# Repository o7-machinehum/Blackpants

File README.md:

# Blackpants
The Blackpants are a carrier board for the [Flipper Blackhat](https://github.com/o7-machinehum/flipper-blackhat). They remove the need for the Flipper Zero itself. This repository was forked from the WHY2025 badge.

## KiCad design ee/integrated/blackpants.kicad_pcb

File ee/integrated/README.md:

# Blackpants hardware

Open **blackpants.kicad_pro** for the active A523 schematic and PCB. It replaces
the A33 hierarchy and uses AXP717C + AXP323 with 2GB LPDDR4.

- [Schematic review PDF](capture/review.pdf)
- [Capture status and interface mapping](capture/README.md)
- [Six-layer layout status and previews](layout/README.md)
- [RAM sourcing](LPDDR4/sourcing.md)
- [Source documents](../../docs/a523/README.md)

All 65 SoC-to-RAM signal paths are connected. There are 139 open connections
overall. Routing remains incomplete; DDR timing and signal/power integrity
have not been approved.

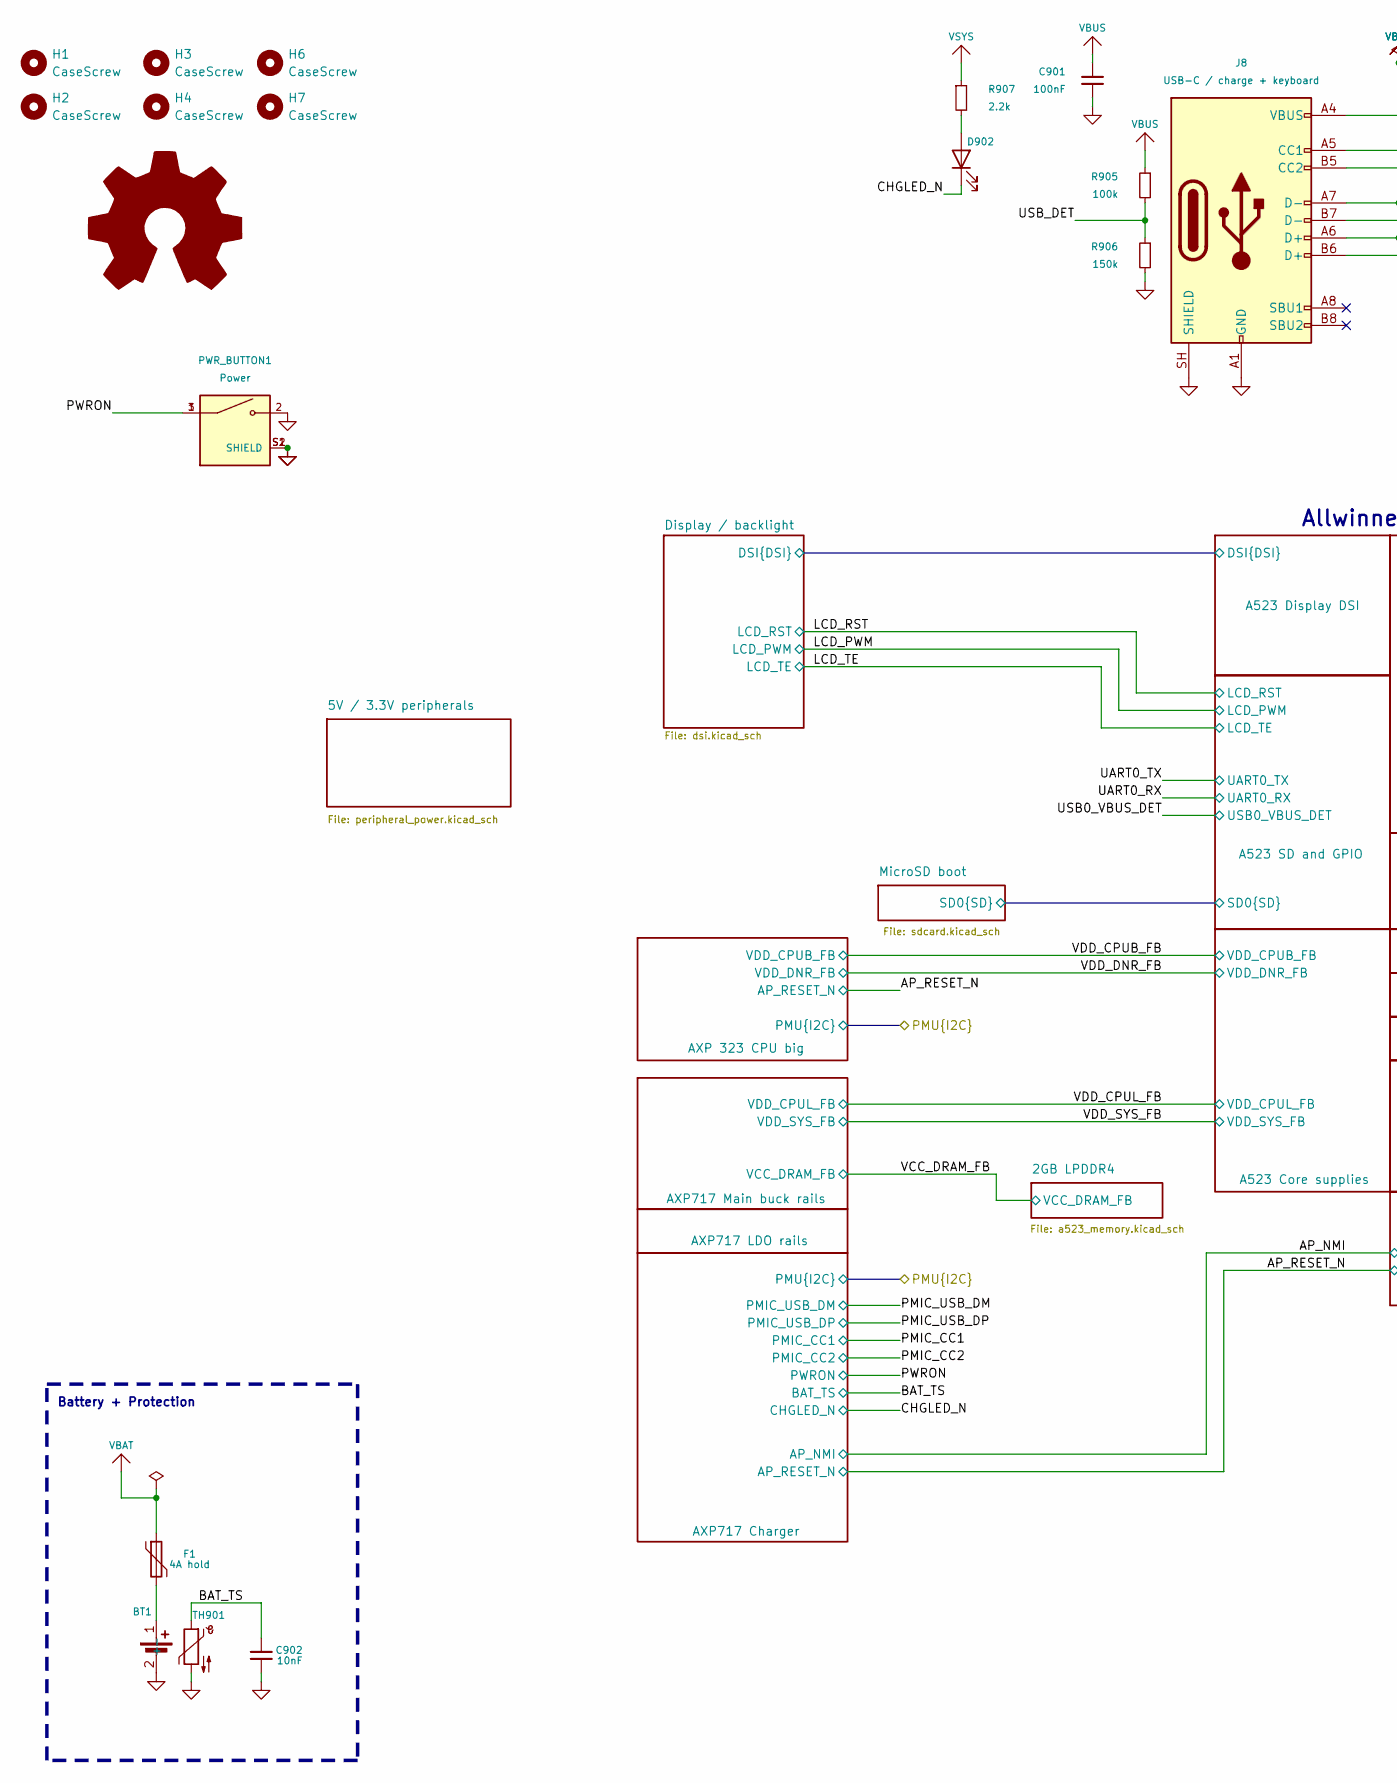
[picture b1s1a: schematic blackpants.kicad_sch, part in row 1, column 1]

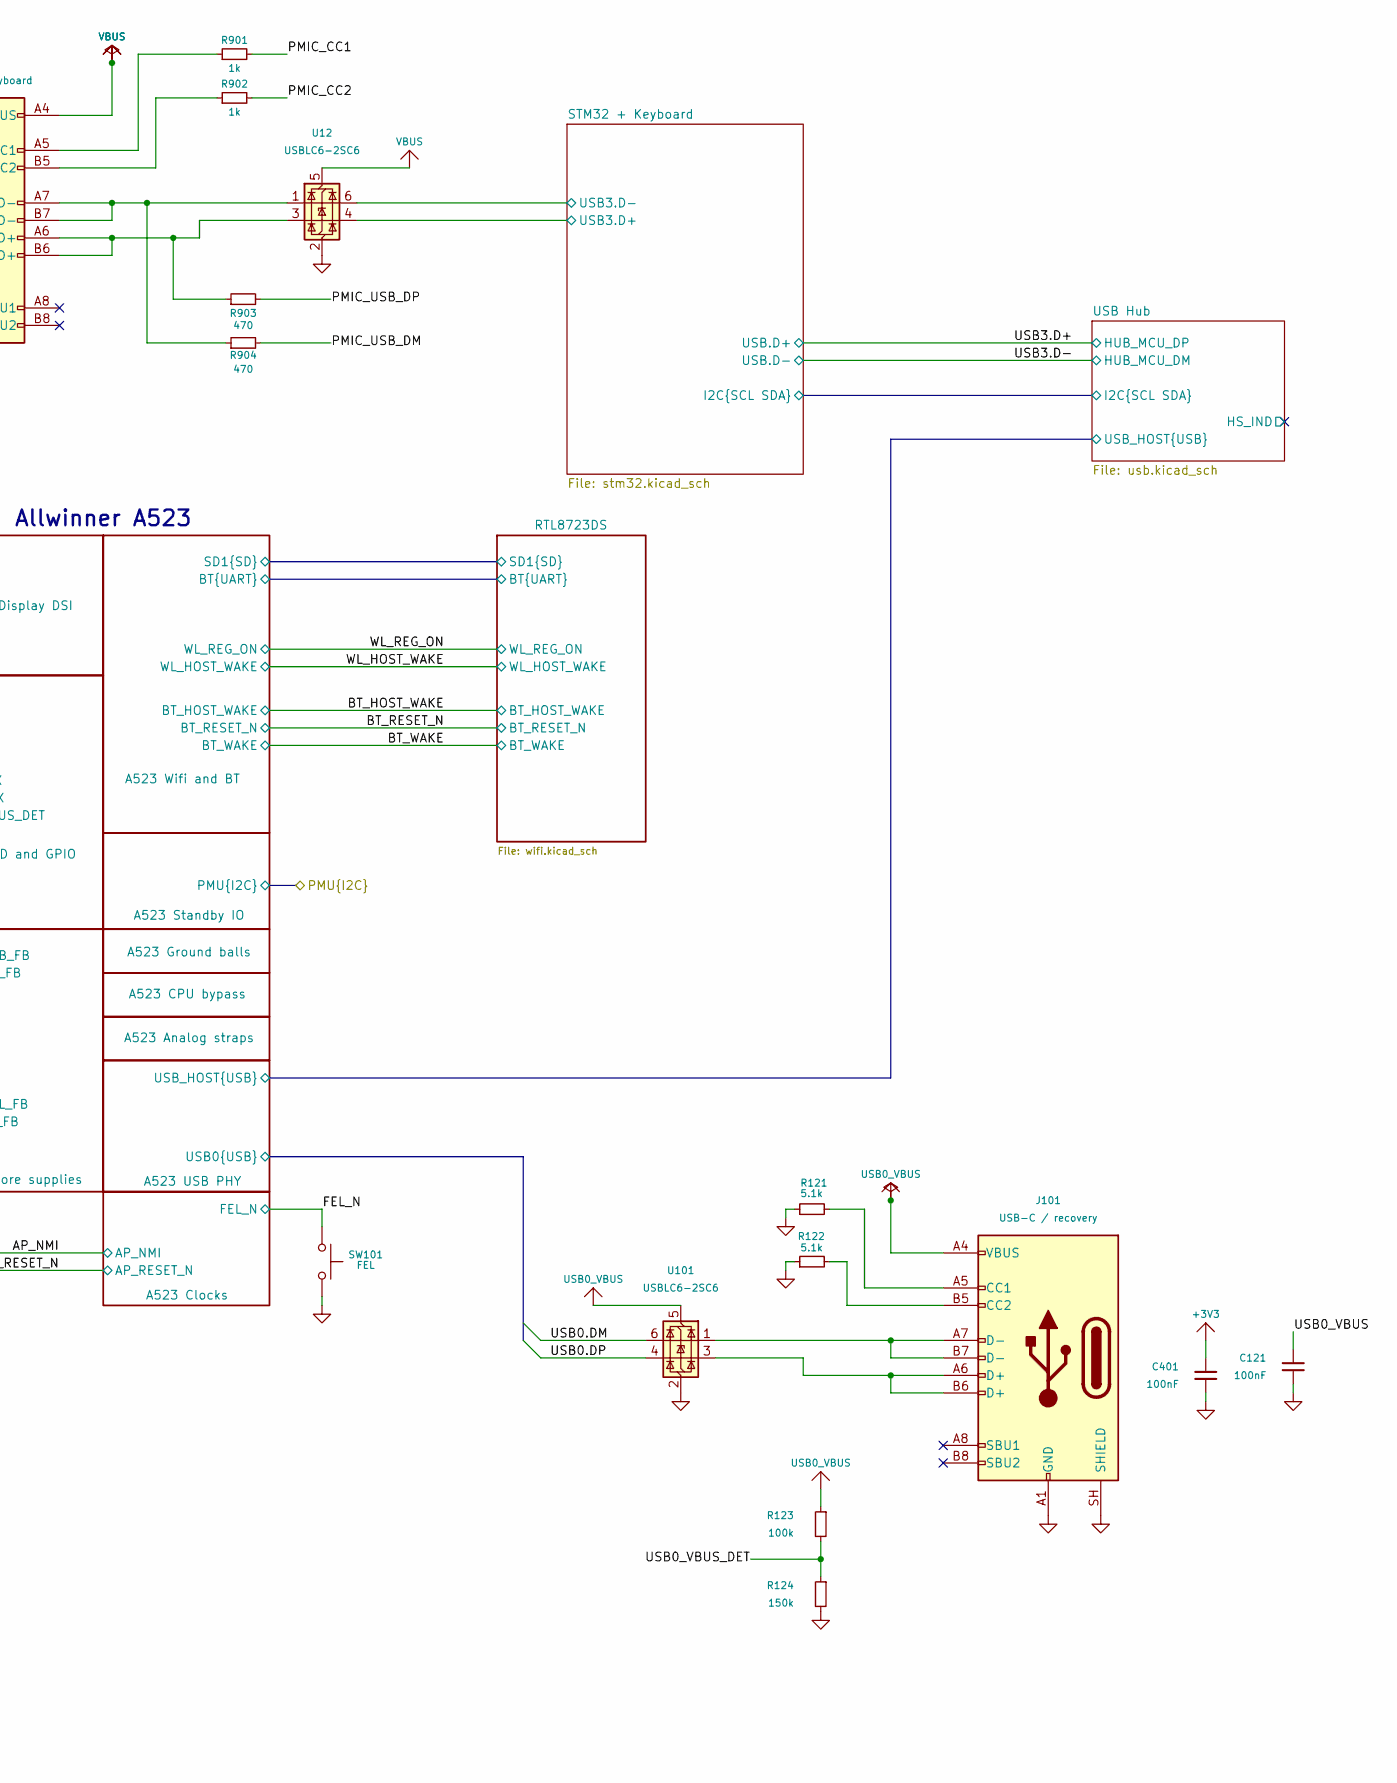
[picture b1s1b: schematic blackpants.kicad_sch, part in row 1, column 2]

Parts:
BT1: Protected 18650 / 1S Li-ion; BH-18650-B1BA002
C121, C401, C901: 100nF; C_0402_1005Metric; Voltage 10V
C902: 10nF; C_0402_1005Metric; Voltage 10V
D902: Charge status; LED_0603_1608Metric
F1: 4A hold; Fuse_1812_4532Metric
H1, H2, H3, H4, H6, H7: CaseScrew; MountingHole_2.7mm_Pad
J8: USB-C / charge + keyboard; USB_C_Receptacle_HRO_TYPE-C-31-M-12
J101: USB-C / recovery; USB_C_Receptacle_GCT_USB4105-xx-A_16P_TopMnt_Horizontal
PWR_BUTTON1: Power; SW_PTS847MM160LSMTR2_LFS; PARTREV B
R121, R122: 5.1k; R_0402_1005Metric
R123, R905: 100k; R_0402_1005Metric
R124, R906: 150k; R_0402_1005Metric
R901, R902: 1k; R_0402_1005Metric
R903, R904: 470; R_0402_1005Metric
R907: 2.2k; R_0402_1005Metric
S1: Logo_Open_Hardware_Large; OSHW-Logo2_24.3x20mm_SilkScreen
SW101: FEL; SW_SPST_TL3342
TH901: 10k @25C / cell-attached NTC; SolderWire-0.5sqmm_1x02_P4.6mm_D0.9mm_OD2.1mm
U12, U101: USBLC6-2SC6; SOT-23-6

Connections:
+3V3: C401.1; also elsewhere on the board
/A523 USB PHY/USB0.DM: U101.6 (I/O1); also elsewhere on the board
/A523 USB PHY/USB0.DP: U101.4 (I/O2); also elsewhere on the board
/BAT_TS: C902.1, TH901.1; also elsewhere on the board
/CHGLED_N: D902.1 (K); also elsewhere on the board
/FEL_N: SW101.1; also elsewhere on the board
/PMIC_CC1: R901.2; also elsewhere on the board
/PMIC_CC2: R902.2; also elsewhere on the board
/PMIC_USB_DM: R904.2; also elsewhere on the board
/PMIC_USB_DP: R903.2; also elsewhere on the board
/PWRON: PWR_BUTTON1.1, PWR_BUTTON1.3; also elsewhere on the board
/STM32 + Keyboard/USB3.D+: U12.4 (I/O2); also elsewhere on the board
/STM32 + Keyboard/USB3.D-: U12.6 (I/O1); also elsewhere on the board
/USB0_VBUS_DET: R123.2, R124.1; also elsewhere on the board
/USB_DET: R905.2, R906.1
GND: BT1.2 (-), C121.2, C401.2, C901.2, C902.2, J8.A1 (GND), J8.A12 (GND), J8.B1 (GND), J8.B12 (GND), J8.SH (SHIELD), J101.A1 (GND), J101.A12 (GND), J101.B1 (GND), J101.B12 (GND), J101.SH (SHIELD), PWR_BUTTON1.2, PWR_BUTTON1.S1 (SHIELD), PWR_BUTTON1.S2 (SHIELD), R121.1, R122.1, R124.2, R906.2, SW101.2, TH901.2, U12.2 (GND), U101.2 (GND); also elsewhere on the board
unnamed: BT1.1 (+), F1.2
unnamed: D902.2 (A), R907.2
unnamed: J8.A5 (CC1), R901.1
unnamed: J8.B5 (CC2), R902.1
unnamed: J8.A6 (D+), J8.B6 (D+), R903.1, U12.3 (I/O2)
unnamed: J8.A7 (D-), J8.B7 (D-), R904.1, U12.1 (I/O1)
unnamed: J101.A5 (CC1), R121.2
unnamed: J101.B5 (CC2), R122.2
unnamed: J101.A6 (D+), J101.B6 (D+), U101.3 (I/O2)
unnamed: J101.A7 (D-), J101.B7 (D-), U101.1 (I/O1)
USB0_VBUS: C121.1, J101.A4 (VBUS), J101.A9 (VBUS), J101.B4 (VBUS), J101.B9 (VBUS), R123.1, U101.5 (VBUS)
VBAT: F1.1; also elsewhere on the board
VBUS: C901.1, J8.A4 (VBUS), J8.A9 (VBUS), J8.B4 (VBUS), J8.B9 (VBUS), R905.1, U12.5 (VBUS); also elsewhere on the board
VSYS: R907.1; also elsewhere on the board

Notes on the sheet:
Battery + Protection
Allwinner A523

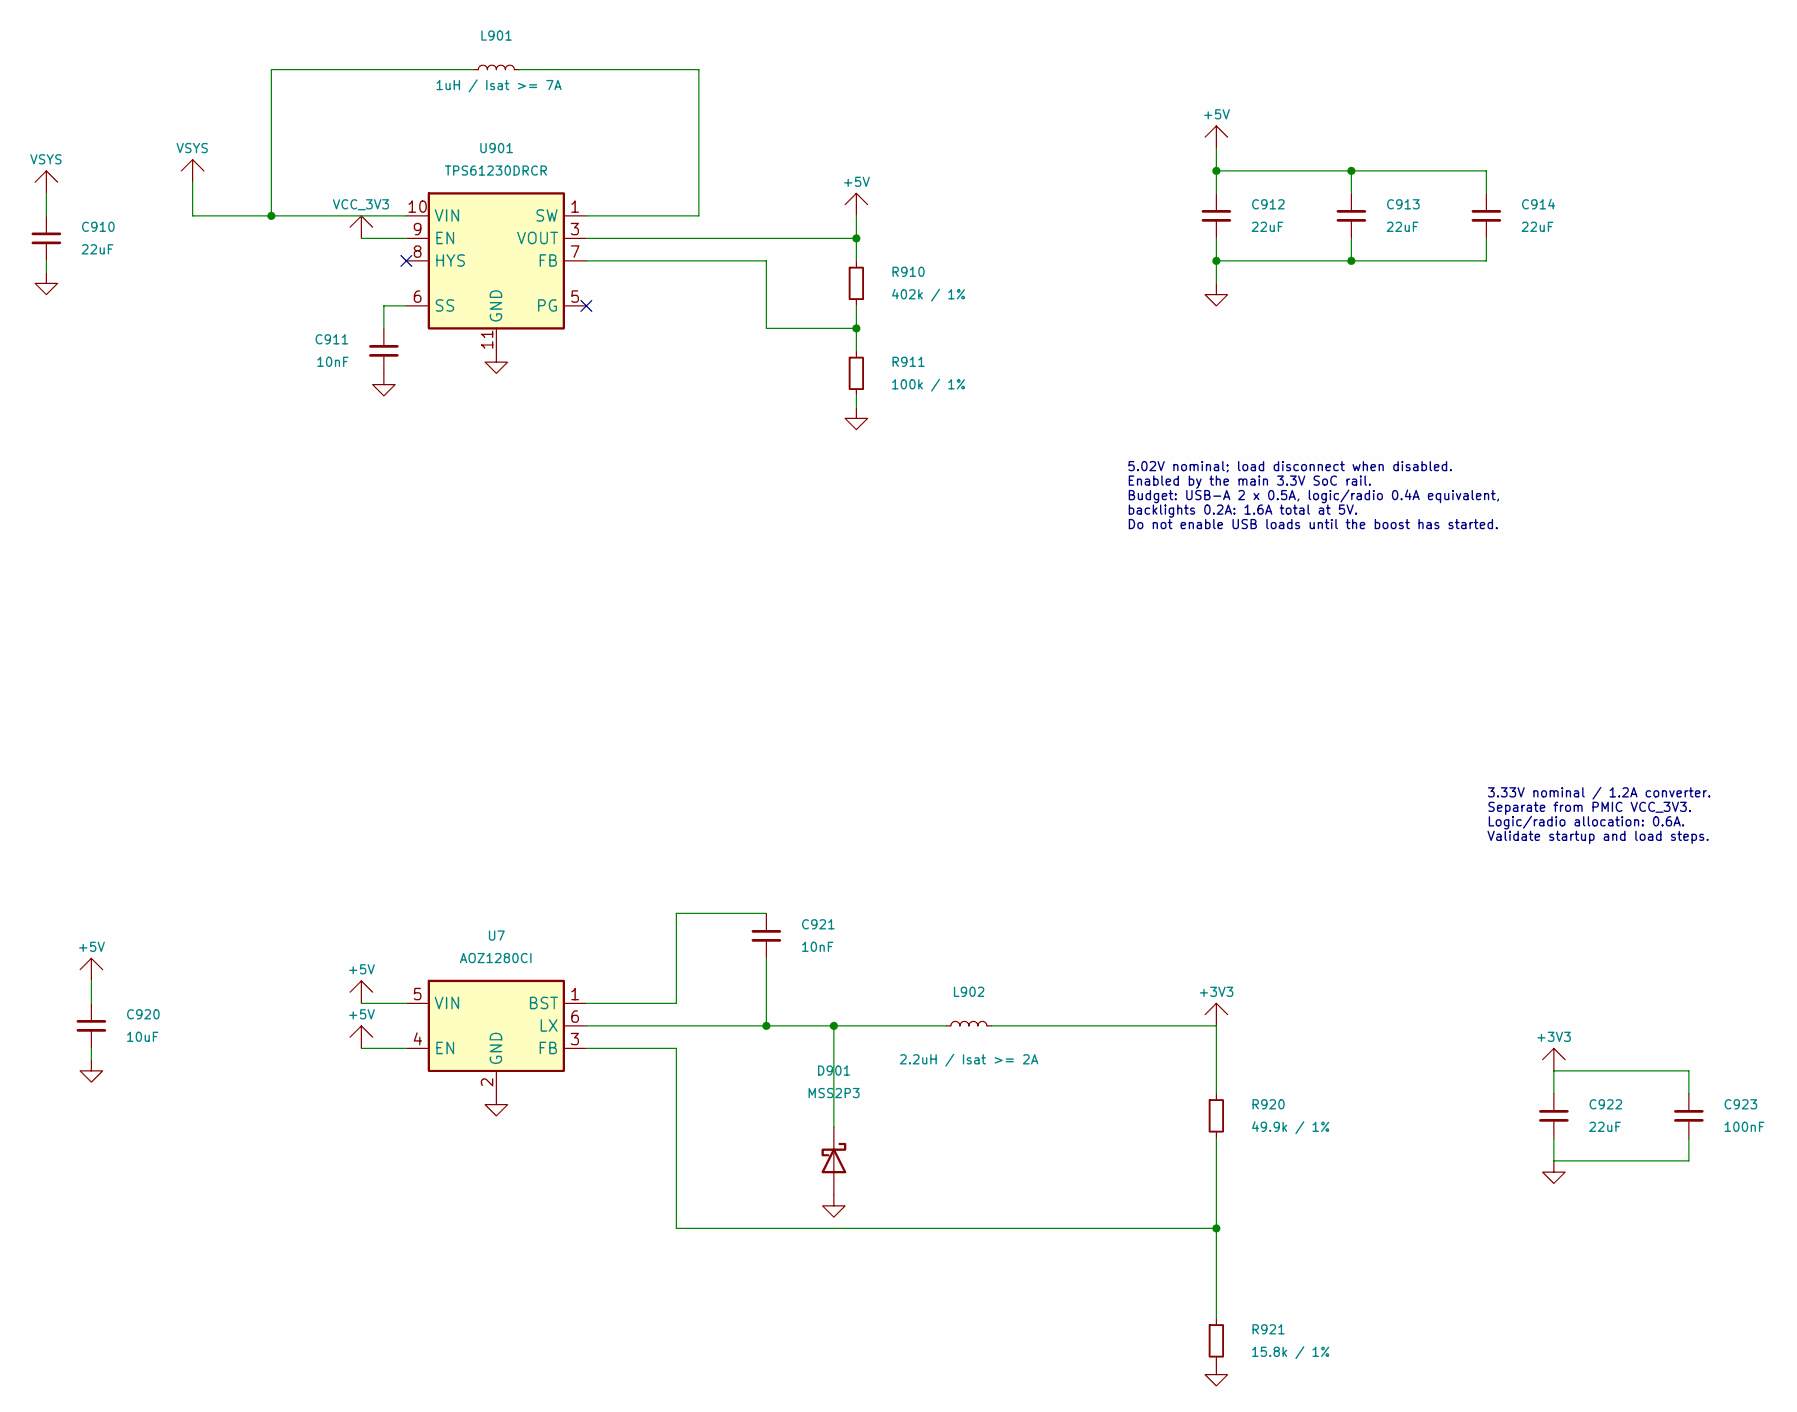
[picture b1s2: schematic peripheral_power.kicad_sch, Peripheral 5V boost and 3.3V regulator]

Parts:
C910, C912, C913, C914: 22uF; C_0805_2012Metric; Voltage 10V
C911, C921: 10nF; C_0402_1005Metric; Voltage 10V
C920: 10uF; C_0603_1608Metric; Voltage 10V
C922: 22uF; C_0603_1608Metric; Voltage 10V
C923: 100nF; C_0402_1005Metric; Voltage 10V
D901: MSS2P3; D_MicroSMP_LargeCathode
L901: 1uH / Isat >= 7A; L_Coilcraft_XAL4020-XXX; MPN XAL4020-102MEB
L902: 2.2uH / Isat >= 2A; L_Coilcraft_XAL4020-XXX
R910: 402k / 1%; R_0402_1005Metric
R911: 100k / 1%; R_0402_1005Metric
R920: 49.9k / 1%; R_0402_1005Metric
R921: 15.8k / 1%; R_0402_1005Metric
U7: AOZ1280CI; SOT-23-6
U901: TPS61230DRCR; Texas_S-PVSON-N10_ThermalVias

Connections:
+3V3: C922.1, C923.1, L902.2, R920.1; also elsewhere on the board
+5V: C912.1, C913.1, C914.1, C920.1, R910.1, U7.4 (EN), U7.5 (VIN), U901.3 (VOUT), U901.4 (VOUT); also elsewhere on the board
GND: C910.2, C911.2, C912.2, C913.2, C914.2, C920.2, C922.2, C923.2, D901.2 (A), R911.2, R921.2, U7.2 (GND), U901.11 (GND); also elsewhere on the board
unnamed: C921.2, D901.1 (K), L902.1, U7.6 (LX)
unnamed: L901.2, U901.1 (SW), U901.2 (SW)
unnamed: C921.1, U7.1 (BST)
unnamed: R920.2, R921.1, U7.3 (FB)
unnamed: R910.2, R911.1, U901.7 (FB)
unnamed: C911.1, U901.6 (SS)
VCC_3V3: U901.9 (EN); also elsewhere on the board
VSYS: C910.1, L901.1, U901.10 (VIN); also elsewhere on the board

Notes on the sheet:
3.33V nominal / 1.2A converter. Separate from PMIC VCC_3V3. Logic/radio allocation: 0.6A. Validate startup and load steps.
5.02V nominal; load disconnect when disabled. Enabled by the main 3.3V SoC rail. Budget: USB-A 2 x 0.5A, logic/radio 0.4A equivalent, backlights 0.2A: 1.6A total at 5V. Do not enable USB loads until the boost has started.

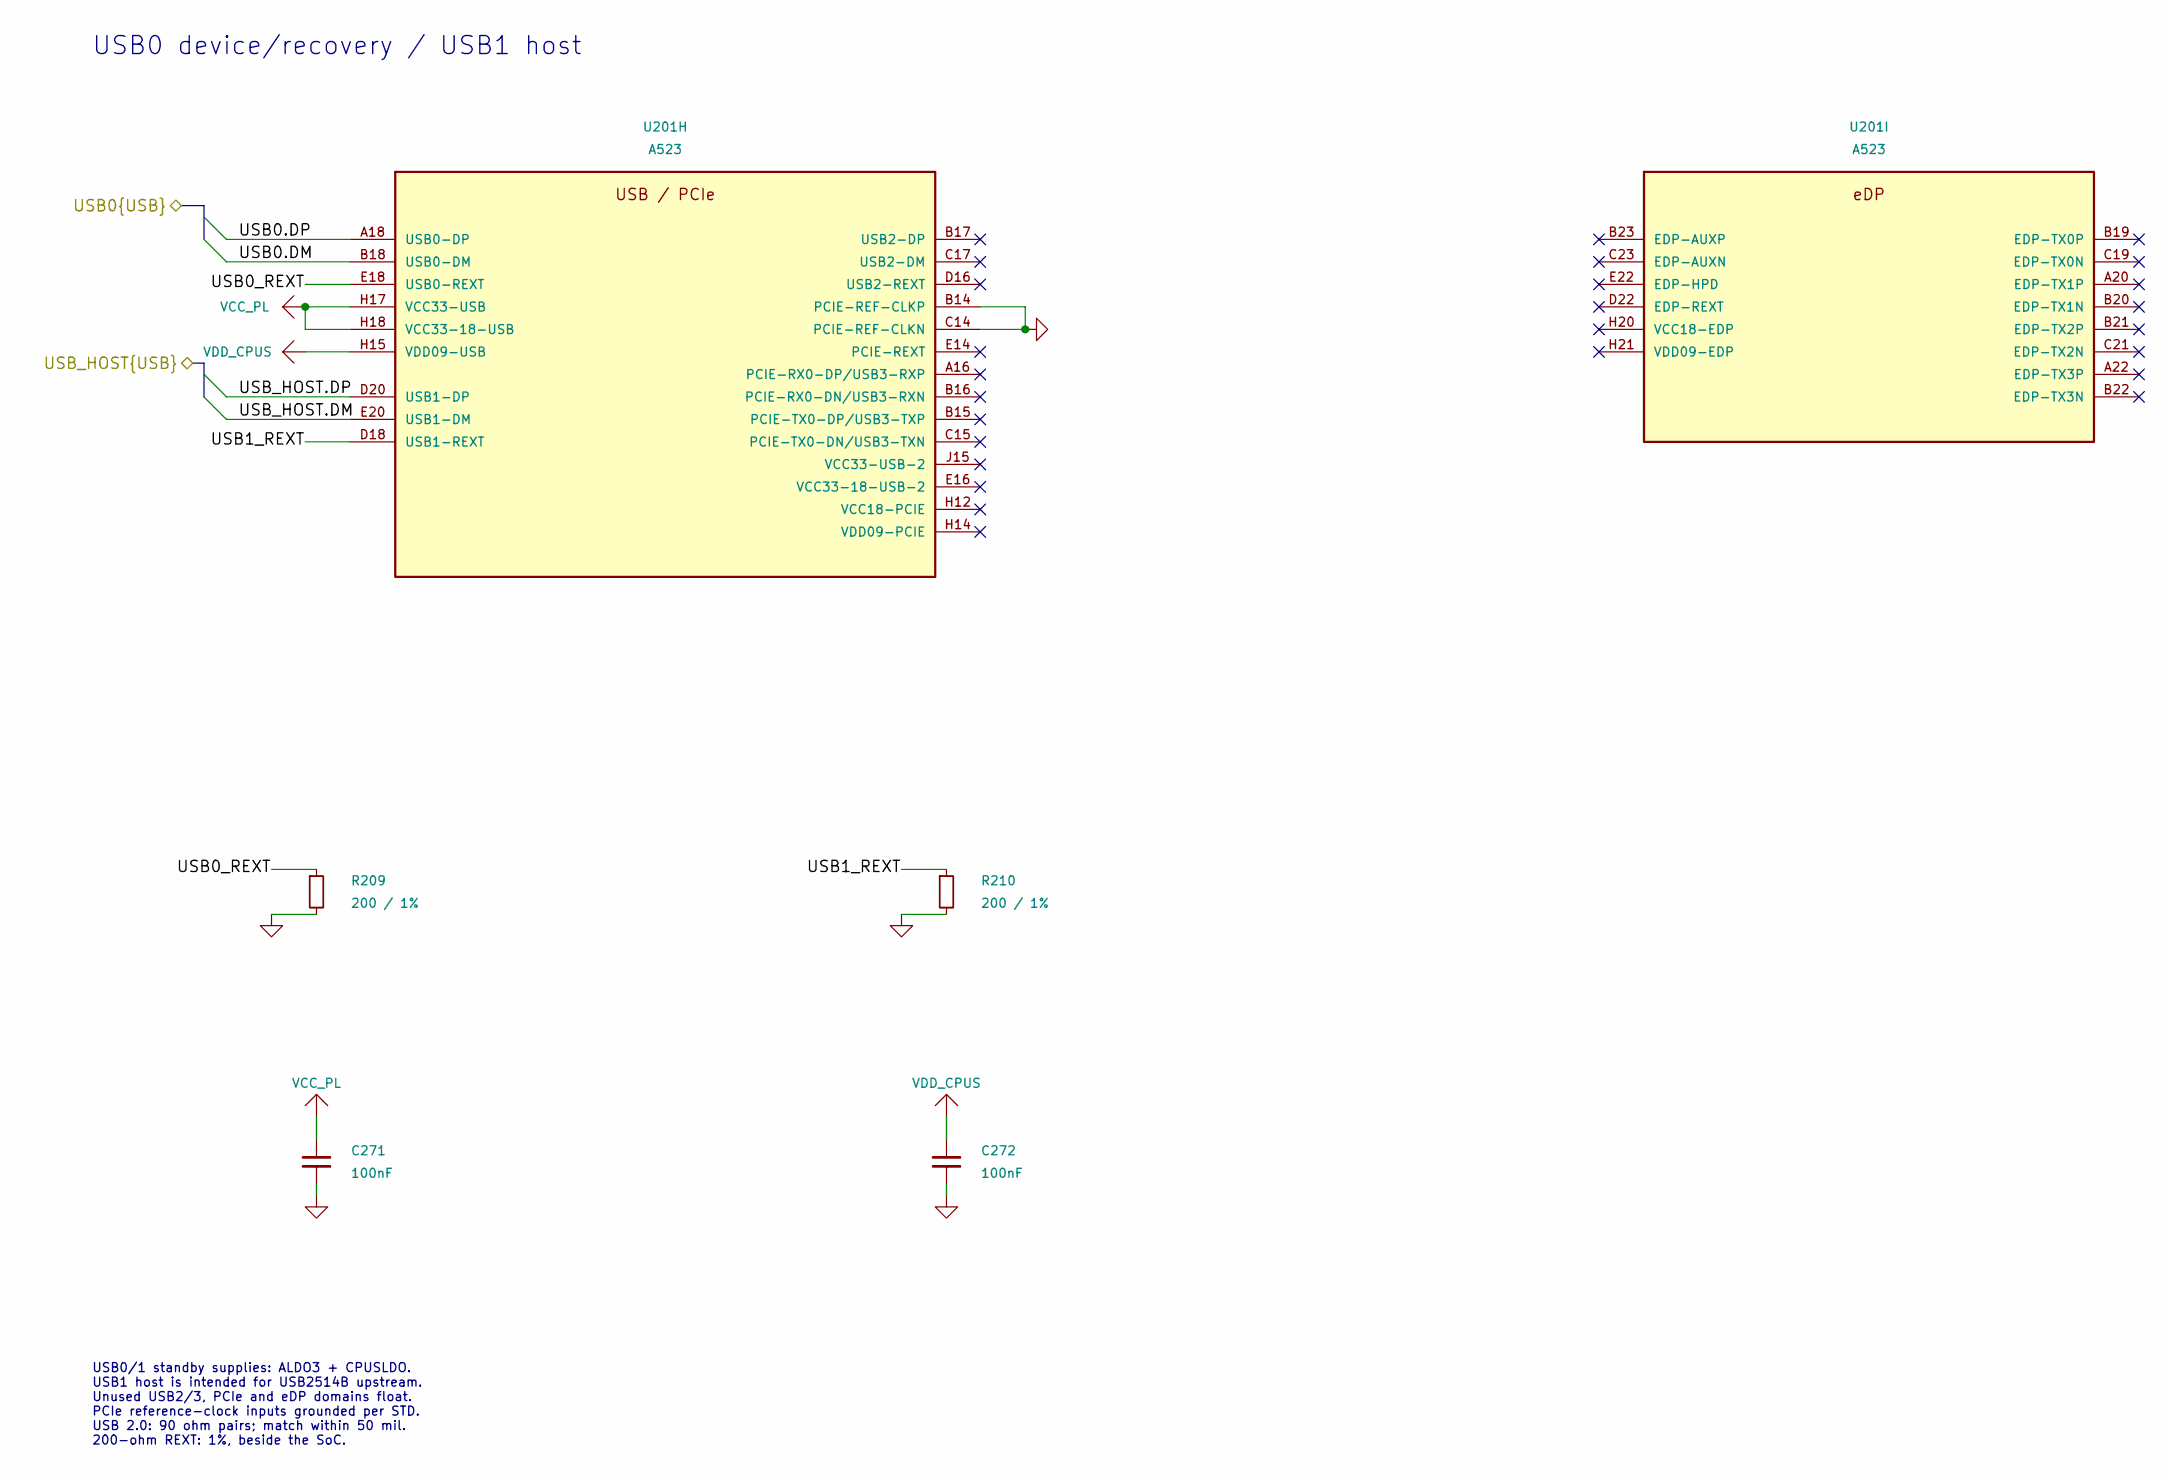
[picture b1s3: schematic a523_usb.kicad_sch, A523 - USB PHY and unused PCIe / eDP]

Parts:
C271, C272: 100nF; C_0201_0603Metric; Voltage 10V
R209, R210: 200 / 1%; R_0402_1005Metric
U201: A523; Allwinner_A523_FCCSP-522_15x15mm_P0.5mm

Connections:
/A523 USB PHY/USB0.DM: U201.B18 (USB0-DM); also elsewhere on the board
/A523 USB PHY/USB0.DP: U201.A18 (USB0-DP); also elsewhere on the board
/A523 USB PHY/USB0_REXT: R209.1, U201.E18 (USB0-REXT)
/A523 USB PHY/USB1_REXT: R210.1, U201.D18 (USB1-REXT)
/A523 USB PHY/USB_HOST.DM: U201.E20 (USB1-DM); also elsewhere on the board
/A523 USB PHY/USB_HOST.DP: U201.D20 (USB1-DP); also elsewhere on the board
GND: C271.2, C272.2, R209.2, R210.2, U201.B14 (PCIE-REF-CLKP), U201.C14 (PCIE-REF-CLKN); also elsewhere on the board
VCC_PL: C271.1, U201.H17 (VCC33-USB), U201.H18 (VCC33-18-USB); also elsewhere on the board
VDD_CPUS: C272.1, U201.H15 (VDD09-USB); also elsewhere on the board

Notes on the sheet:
USB0 device/recovery / USB1 host
USB0/1 standby supplies: ALDO3 + CPUSLDO. USB1 host is intended for USB2514B upstream. Unused USB2/3, PCIe and eDP domains float. PCIe reference-clock inputs grounded per STD. USB 2.0: 90 ohm pairs; match within 50 mil. 200-ohm REXT: 1%, beside the SoC.

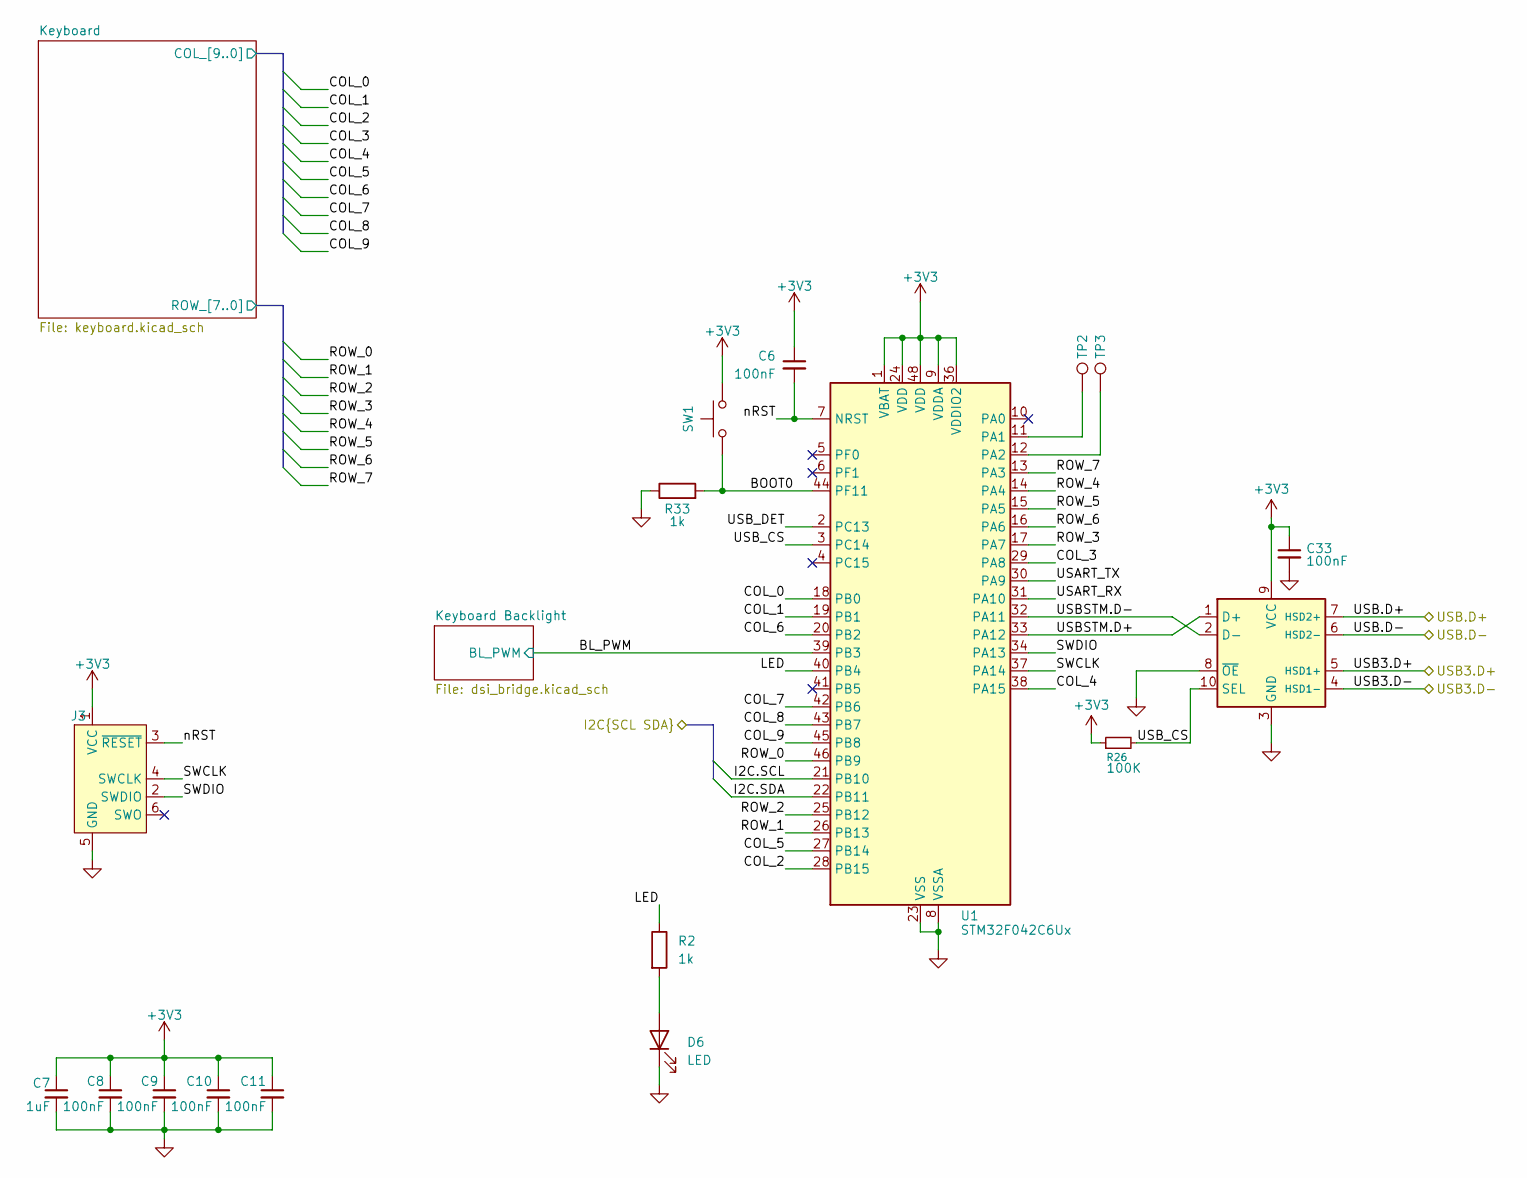
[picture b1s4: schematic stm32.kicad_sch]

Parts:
C6, C8, C9, C10, C11, C33: 100nF; C_0402_1005Metric; MPN CL05B104KB54PNC
C7: 1uF; C_0402_1005Metric; MPN CL05B105KQ5NQNC
D6: LED; LED_0603_1608Metric; MPN KT-0603R
J3: Conn_ARM_SWD_TagConnect_TC2030-NL; Tag-Connect_TC2030-IDC-NL_2x03_P1.27mm_Vertical
R2, R33: 1k; R_0402_1005Metric; MPN 0402WGF1001TCE
R26: 100K; R_0402_1005Metric; MPN RC0402FR-13100KL
SW1: SW_Push; SW_Push_1P1T_NO_CK_KSC7xxJ; MPN KSC741JLFS
TP2, TP3: TestPoint; TestPoint_Pad_1.0x1.0mm
U1: STM32F042C6Ux; QFN-48-1EP_7x7mm_P0.5mm_EP5.6x5.6mm; MPN STM32F042C6U6
U11: TPSGM7227YUWQ10G; UQFN-10_1.4x1.8mm_P0.4mm; MPN TPSGM7227YUWQ10G

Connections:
+3V3: C6.1, C7.1, C8.1, C9.1, C10.1, C11.1, C33.1, J3.1 (VCC), R26.1, SW1.2, U1.1 (VBAT), U1.9 (VDDA), U1.24 (VDD), U1.36 (VDDIO2), U1.48 (VDD), U11.9 (VCC); also elsewhere on the board
/STM32 + Keyboard/BL_PWM: U1.39 (PB3); also elsewhere on the board
/STM32 + Keyboard/BOOT0: R33.2, SW1.1, U1.44 (PF11)
/STM32 + Keyboard/I2C.SCL: U1.21 (PB10); also elsewhere on the board
/STM32 + Keyboard/I2C.SDA: U1.22 (PB11); also elsewhere on the board
/STM32 + Keyboard/Keyboard/COL_0: U1.18 (PB0); also elsewhere on the board
/STM32 + Keyboard/Keyboard/COL_1: U1.19 (PB1); also elsewhere on the board
/STM32 + Keyboard/Keyboard/COL_2: U1.28 (PB15); also elsewhere on the board
/STM32 + Keyboard/Keyboard/COL_3: U1.29 (PA8); also elsewhere on the board
/STM32 + Keyboard/Keyboard/COL_4: U1.38 (PA15); also elsewhere on the board
/STM32 + Keyboard/Keyboard/COL_5: U1.27 (PB14); also elsewhere on the board
/STM32 + Keyboard/Keyboard/COL_6: U1.20 (PB2); also elsewhere on the board
/STM32 + Keyboard/Keyboard/COL_7: U1.42 (PB6); also elsewhere on the board
/STM32 + Keyboard/Keyboard/COL_8: U1.43 (PB7); also elsewhere on the board
/STM32 + Keyboard/Keyboard/COL_9: U1.45 (PB8); also elsewhere on the board
/STM32 + Keyboard/Keyboard/ROW_0: U1.46 (PB9); also elsewhere on the board
/STM32 + Keyboard/Keyboard/ROW_1: U1.26 (PB13); also elsewhere on the board
/STM32 + Keyboard/Keyboard/ROW_2: U1.25 (PB12); also elsewhere on the board
/STM32 + Keyboard/Keyboard/ROW_3: U1.17 (PA7); also elsewhere on the board
/STM32 + Keyboard/Keyboard/ROW_4: U1.14 (PA4); also elsewhere on the board
/STM32 + Keyboard/Keyboard/ROW_5: U1.15 (PA5); also elsewhere on the board
/STM32 + Keyboard/Keyboard/ROW_6: U1.16 (PA6); also elsewhere on the board
/STM32 + Keyboard/Keyboard/ROW_7: U1.13 (PA3); also elsewhere on the board
/STM32 + Keyboard/LED: R2.1, U1.40 (PB4)
/STM32 + Keyboard/SWCLK: J3.4 (SWCLK), U1.37 (PA14)
/STM32 + Keyboard/SWDIO: J3.2 (SWDIO), U1.34 (PA13)
/STM32 + Keyboard/USART_RX: U1.31 (PA10)
/STM32 + Keyboard/USART_TX: U1.30 (PA9)
/STM32 + Keyboard/USB3.D+: U11.5 (HSD1+); also elsewhere on the board
/STM32 + Keyboard/USB3.D-: U11.4 (HSD1-); also elsewhere on the board
/STM32 + Keyboard/USBSTM.D+: U1.33 (PA12), U11.1 (D+)
/STM32 + Keyboard/USBSTM.D-: U1.32 (PA11), U11.2 (D-)
/STM32 + Keyboard/USB_CS: R26.2, U1.3 (PC14), U11.10 (SEL)
/STM32 + Keyboard/USB_DET: U1.2 (PC13)
/STM32 + Keyboard/nRST: C6.2, J3.3 (~RESET), U1.7 (NRST)
/USB3.D+: U11.7 (HSD2+); also elsewhere on the board
/USB3.D-: U11.6 (HSD2-); also elsewhere on the board
GND: C7.2, C8.2, C9.2, C10.2, C11.2, C33.2, D6.1 (K), J3.5 (GND), R33.1, U1.8 (VSSA), U1.23 (VSS), U1.35 (VSS), U1.47 (VSS), U1.49 (VSS), U11.3 (GND), U11.8 (~OE); also elsewhere on the board
unnamed: D6.2 (A), R2.2
unnamed: TP2.1 (1_1), U1.11 (PA1)
unnamed: TP3.1 (1_1), U1.12 (PA2)

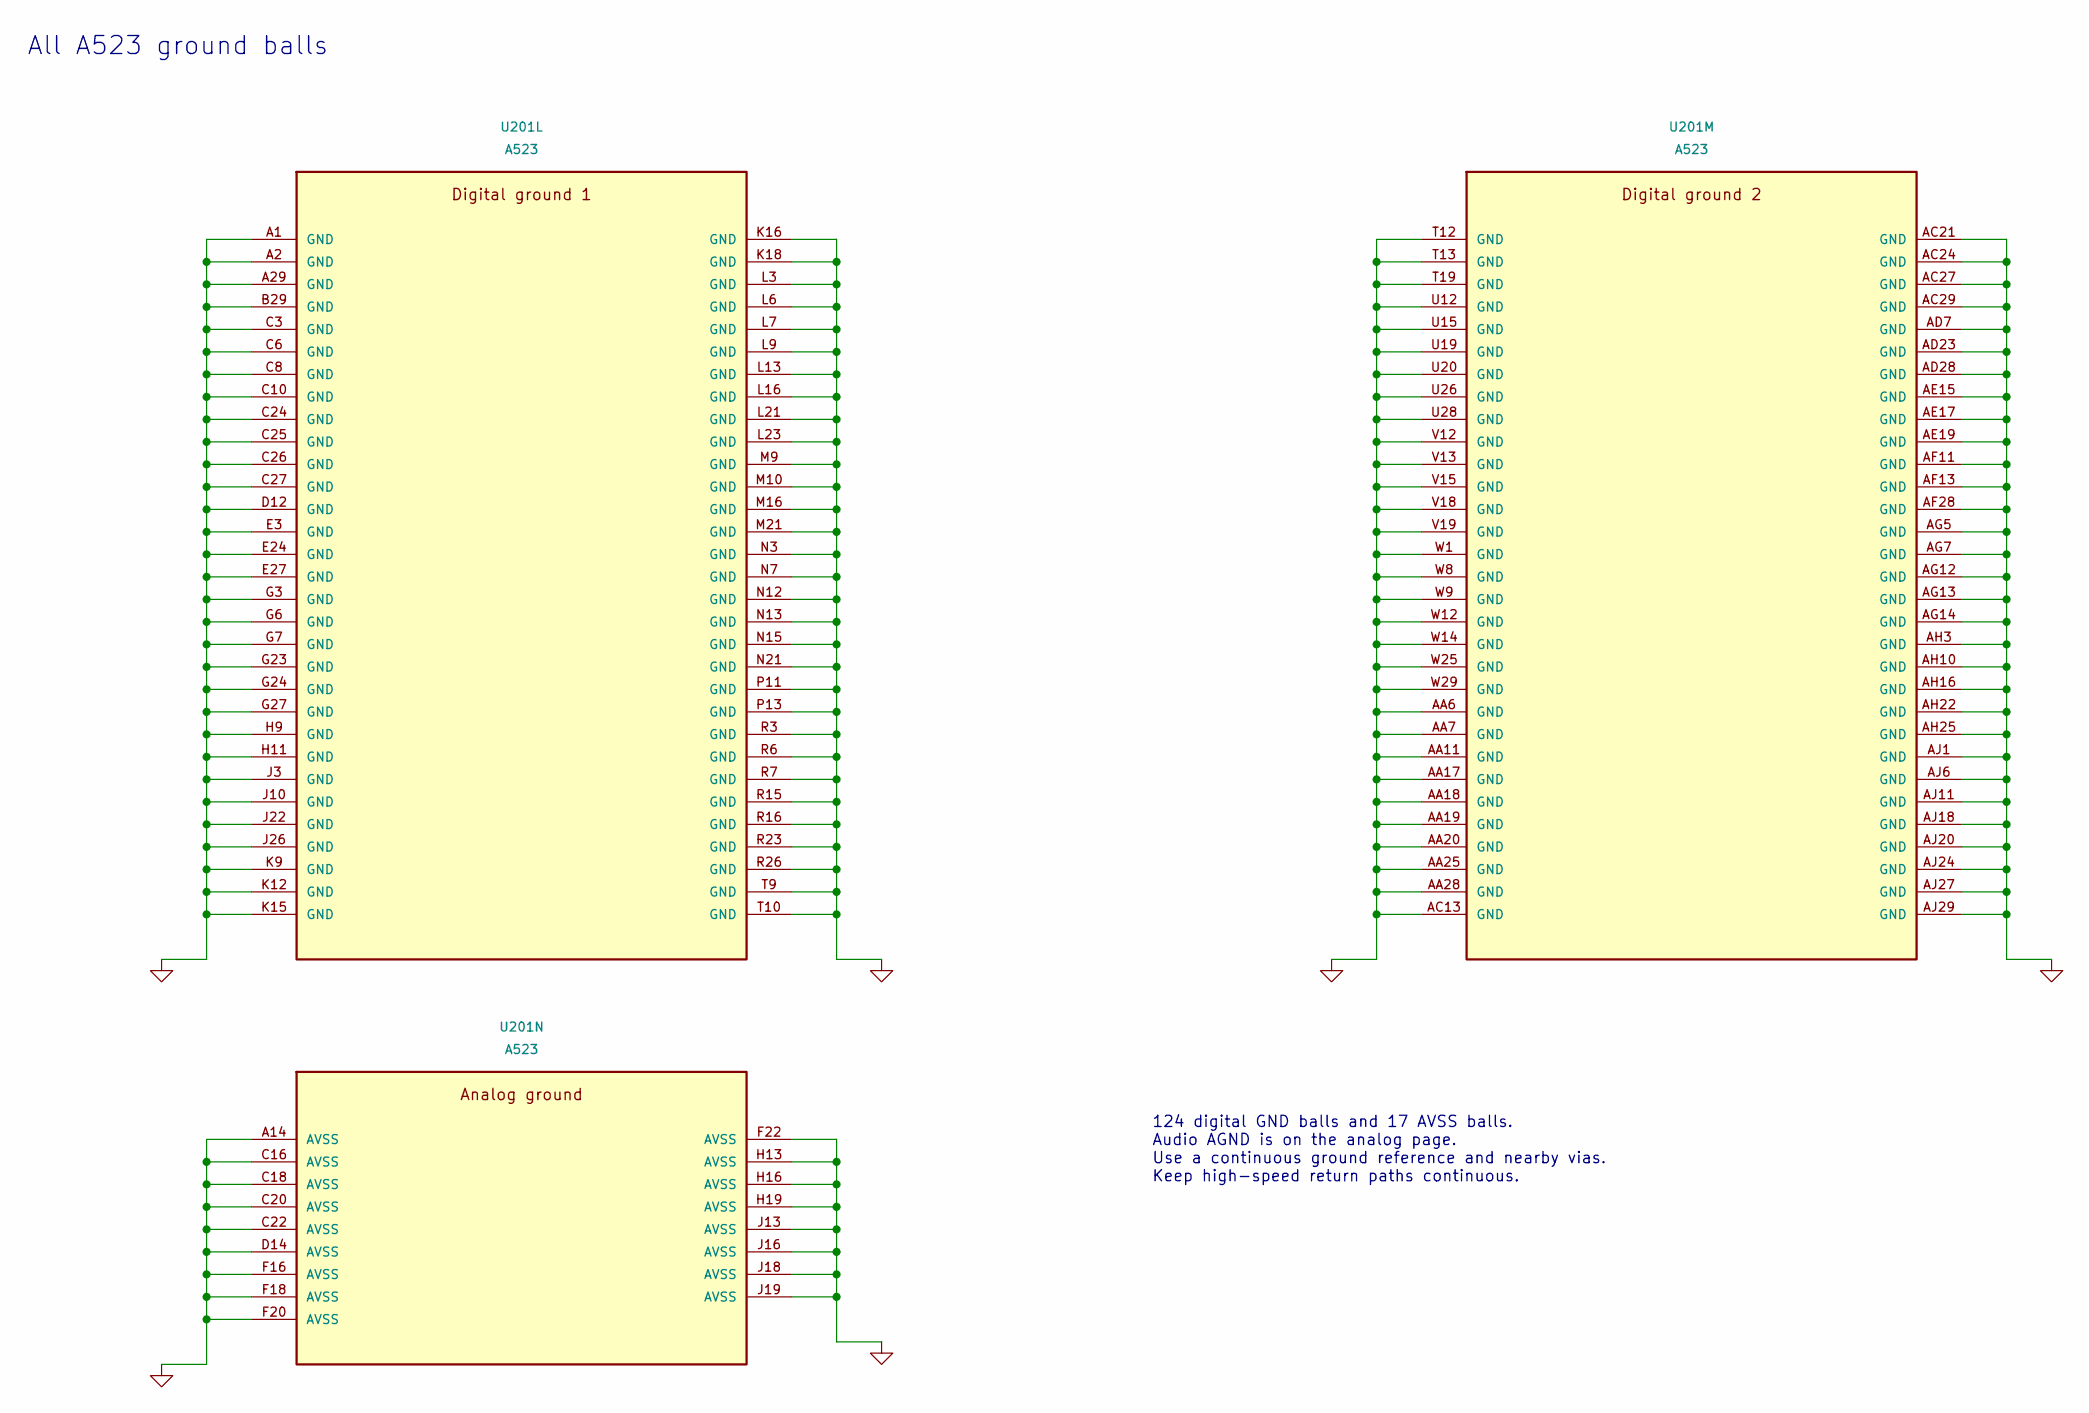
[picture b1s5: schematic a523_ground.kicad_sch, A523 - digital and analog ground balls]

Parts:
U201: A523; Allwinner_A523_FCCSP-522_15x15mm_P0.5mm

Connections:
GND: U201.A1 (GND), U201.A2 (GND), U201.A14 (AVSS), U201.A29 (GND), U201.AA6 (GND), U201.AA7 (GND), U201.AA11 (GND), U201.AA17 (GND), U201.AA18 (GND), U201.AA19 (GND), U201.AA20 (GND), U201.AA25 (GND), U201.AA28 (GND), U201.AC13 (GND), U201.AC21 (GND), U201.AC24 (GND), U201.AC27 (GND), U201.AC29 (GND), U201.AD7 (GND), U201.AD23 (GND), U201.AD28 (GND), U201.AE15 (GND), U201.AE17 (GND), U201.AE19 (GND), U201.AF11 (GND), U201.AF13 (GND), U201.AF28 (GND), U201.AG5 (GND), U201.AG7 (GND), U201.AG12 (GND), U201.AG13 (GND), U201.AG14 (GND), U201.AH3 (GND), U201.AH10 (GND), U201.AH16 (GND), U201.AH22 (GND), U201.AH25 (GND), U201.AJ1 (GND), U201.AJ6 (GND), U201.AJ11 (GND), U201.AJ18 (GND), U201.AJ20 (GND), U201.AJ24 (GND), U201.AJ27 (GND), U201.AJ29 (GND), U201.B29 (GND), U201.C3 (GND), U201.C6 (GND), U201.C8 (GND), U201.C10 (GND), U201.C16 (AVSS), U201.C18 (AVSS), U201.C20 (AVSS), U201.C22 (AVSS), U201.C24 (GND), U201.C25 (GND), U201.C26 (GND), U201.C27 (GND), U201.D12 (GND), U201.D14 (AVSS), U201.E3 (GND), U201.E24 (GND), U201.E27 (GND), U201.F16 (AVSS), U201.F18 (AVSS), U201.F20 (AVSS), U201.F22 (AVSS), U201.G3 (GND), U201.G6 (GND), U201.G7 (GND), U201.G23 (GND), U201.G24 (GND), U201.G27 (GND), U201.H9 (GND), U201.H11 (GND), U201.H13 (AVSS), U201.H16 (AVSS), U201.H19 (AVSS), U201.J3 (GND), U201.J10 (GND), U201.J13 (AVSS), U201.J16 (AVSS), U201.J18 (AVSS), U201.J19 (AVSS), U201.J22 (GND), U201.J26 (GND), U201.K9 (GND), U201.K12 (GND), U201.K15 (GND), U201.K16 (GND), U201.K18 (GND), U201.L3 (GND), U201.L6 (GND), U201.L7 (GND), U201.L9 (GND), U201.L13 (GND), U201.L16 (GND), U201.L21 (GND), U201.L23 (GND), U201.M9 (GND), U201.M10 (GND), U201.M16 (GND), U201.M21 (GND), U201.N3 (GND), U201.N7 (GND), U201.N12 (GND), U201.N13 (GND), U201.N15 (GND), U201.N21 (GND), U201.P11 (GND), U201.P13 (GND), U201.R3 (GND), U201.R6 (GND), U201.R7 (GND), U201.R15 (GND), U201.R16 (GND), U201.R23 (GND), U201.R26 (GND), U201.T9 (GND), U201.T10 (GND), U201.T12 (GND), U201.T13 (GND), U201.T19 (GND), U201.U12 (GND), U201.U15 (GND), U201.U19 (GND), U201.U20 (GND), U201.U26 (GND), U201.U28 (GND), U201.V12 (GND), U201.V13 (GND), U201.V15 (GND), U201.V18 (GND), U201.V19 (GND), U201.W1 (GND), U201.W8 (GND), U201.W9 (GND), U201.W12 (GND), U201.W14 (GND), U201.W25 (GND), U201.W29 (GND); also elsewhere on the board

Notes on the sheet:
124 digital GND balls and 17 AVSS balls. Audio AGND is on the analog page. Use a continuous ground reference and nearby vias. Keep high-speed return paths continuous.
All A523 ground balls
